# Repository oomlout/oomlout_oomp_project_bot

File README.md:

# oomlout_oomp_documentation_bot_v2

## actions

* action_setup.py -- sets up data and structure
* action_generate_kicad_from_eagle.py -- take all .brd eagle files, open in kicad and save as kicad_pcb and a kicad_sch file
* action_generate_kicad_outputs.py -- (not used anymore) generate the outputs using robo mouse, takes in a kicad_pcb and kicad_sch file
* action_generate_kibot_outputs.py -- all directories with kicad_pcb files get the kibot template from templates/kibot_template.yaml copied to them and kibot is run if the report.txt doesn't exist
* action_generate_image_resolutions.py -- generate resolutions of images
* action_generate_readmes -- generate all the readmes
* action_cleanup_project.py -- cleans up unwanted files from a project directory
* action_harvest_parts.py -- take the working_bom.csv and add parts_verbose to yaml file
* action_match_parts.py -- go trhough each part and match parts_verbose aprts with parts_oomp
* action_find_part.py -- go through all projects and compile a list of all the entries with  search term
* action_rescue_old_kicad_schematic.py -- go through and find all directories that have a kicad_pcb and a .sch file and no schematics generated. Open in kicad 5 and save.

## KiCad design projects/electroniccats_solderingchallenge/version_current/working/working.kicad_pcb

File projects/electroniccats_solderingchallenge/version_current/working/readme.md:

# OOMP Project  
## SolderingChallenge  by ElectronicCats  
  
oomp key: oomp_projects_flat_electroniccats_solderingchallenge  
(snippet of original readme)  
  
Introduction  
============  
  
This design is based on the work of [aspro648](https://github.com/aspro648) you can support him buying his stuff at [Tindie](https://www.tindie.com/products/MakersBox/smd-challenge/)  
  
This design was possible thanks to [Mouser electronics](https://iopscience.iop.org/journal/2041-8205/page/Focus_on_EHT), [Würth Elektronik](https://www.we-online.com/web/en/electronic_components/willkommen_pbs/Welcome.php) and [Makers GDL](https://makersgdl.com/) we really appreciate all your support to get this boards free for the Talent Land 2019.  

Test your surface mount soldering skills out, starting with a 1206 package and work your way down into the humanly possible solder device, the 0402. Powered by a CR2032 coin cell and Attiny 85 SOIC.   

Design Files  
============  
This project is designed using Open Source [KiCad](http://kicad.org/). Design files are located in the [Hw](Hw/) folder.  You can oogle the [schematic](Images/solderingChallenge.pdf).  
  
Firmware  
========  
This project is programed using the Open Source [Arduino](https://www.arduino.cc/). I use my Open Source [AVR Programming Shield](https://www.tindie.com/products/MakersBox/yet-another-programming-shield/) to program the Attiny. The firmware is located in the [firmware](Fw/) folder.  
  
Assembly Instructions  
=====================  
[Aspro648](https://github.com/aspro648) hav  
  full source readme at [readme_src.md](readme_src.md)  
  
source repo at: [https://github.com/ElectronicCats/SolderingChallenge](https://github.com/ElectronicCats/SolderingChallenge)  
## Board  

## Schematic  

[schematic pdf](working_schematic.pdf)  
## Images

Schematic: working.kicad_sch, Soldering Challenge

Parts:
BT1: Battery_Cell; 79523141
C1: 0.1uF; C_0805_2012Metric_Pad1.15x1.40mm_HandSolder
D1: 1206; LED_1206_3216Metric_Pad1.42x1.75mm_HandSolder
D2: 0805; LED_0805_2012Metric_Pad1.15x1.40mm_HandSolder
D3: 0603; LED_0603_1608Metric_Pad1.05x0.95mm_HandSolder
D4: 0402; LED_0402_1005Metric
J1: ISP; PinHeader_2x03_P2.54mm_Vertical
R1: 1206; R_1206_3216Metric_Pad1.42x1.75mm_HandSolder
R2: 0805; R_0805_2012Metric_Pad1.15x1.40mm_HandSolder
R3: 0603; R_0603_1608Metric_Pad1.05x0.95mm_HandSolder
R4: 0402; R_0402_1005Metric
TP1: PB0; TestPoint_Pad_1.0x1.0mm
TP2: PB1; TestPoint_Pad_1.0x1.0mm
TP3: PB2; TestPoint_Pad_1.0x1.0mm
TP4: PB3; TestPoint_Pad_1.0x1.0mm
TP5: PB4; TestPoint_Pad_1.0x1.0mm
TP6, TP7, TP8, TP9, TP10: GND; TestPoint_Pad_1.0x1.0mm
U1: ATtiny85-20SU; SOIJ-8_5.3x5.3mm_P1.27mm

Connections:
/MISO: D2.2 (A), J1.1, TP2.1, U1.6
/MOSI: D3.2 (A), J1.4, TP1.1, U1.5
/PB2: D1.2 (A), J1.3, TP3.1, U1.7
/PB3: D4.2 (A), TP4.1, U1.2
/PB4: U1.3
/RST: J1.5, U1.1
GND: BT1.2 (-), C1.2, J1.6, R1.1, R2.1, R3.1, R4.1, TP6.1, TP7.1, TP8.1, TP9.1, TP10.1, U1.4
unnamed: D1.1 (K), R1.2
unnamed: D2.1 (K), R2.2
unnamed: D3.1 (K), R3.2
unnamed: D4.1 (K), R4.2
VCC: BT1.1 (+), C1.1, J1.2, U1.8

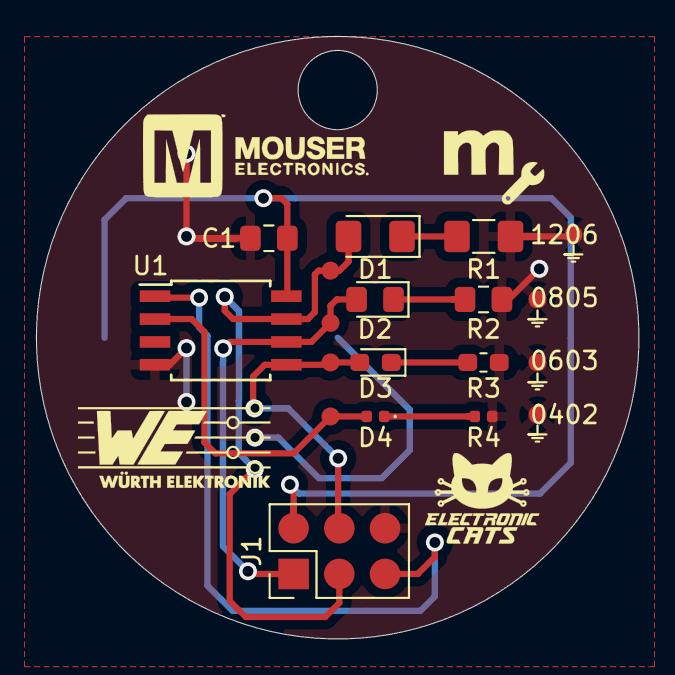
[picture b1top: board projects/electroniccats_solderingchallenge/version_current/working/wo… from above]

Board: 2 copper layers, 33.5 x 33.5 mm, 20 parts (1 on the bottom side), 11 nets.

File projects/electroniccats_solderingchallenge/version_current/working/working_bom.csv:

"Id";"Designator";"Footprint";"Quantity";"Designation";"Supplier and ref";
1;"R1";"R_1206_3216Metric_Pad1.42x1.75mm_HandSolder";1;"1206";;;
2;"R4";"R_0402_1005Metric";1;"0402";;;
3;"U1";"SOIJ-8_5.3x5.3mm_P1.27mm";1;"ATtiny85-20SU";;;
4;"D2";"LED_0805_2012Metric_Pad1.15x1.40mm_HandSolder";1;"0805";;;
5;"D3";"LED_0603_1608Metric_Pad1.05x0.95mm_HandSolder";1;"0603";;;
6;"D4";"LED_0402_1005Metric";1;"0402";;;
7;"R3";"R_0603_1608Metric_Pad1.05x0.95mm_HandSolder";1;"0603";;;
8;"R2";"R_0805_2012Metric_Pad1.15x1.40mm_HandSolder";1;"0805";;;
9;"C1";"C_0805_2012Metric_Pad1.15x1.40mm_HandSolder";1;"0.1uF";;;
10;"J1";"PinHeader_2x03_P2.54mm_Vertical";1;"ISP";;;
11;"G***,G***";"makersGDL";2;"LOGO";;;
12;"D1";"LED_1206_3216Metric_Pad1.42x1.75mm_HandSolder";1;"1206";;;
13;"G***,G***";"mouser";2;"LOGO";;;
14;"G***,G***";"electronic_cats_logo_4x3";2;"LOGO";;;
15;"G***,G***";"wurth";2;"LOGO";;;
16;"BT1";"79523141";1;"Battery_Cell";;;

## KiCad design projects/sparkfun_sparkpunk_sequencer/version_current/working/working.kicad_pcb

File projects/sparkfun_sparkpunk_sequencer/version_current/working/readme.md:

# Sparkpunk_Sequencer by sparkfun  
This is a harvested standardized copy of a project from github.  
The original project can be found at:  
https://github.com/sparkfun/Sparkpunk_Sequencer  
Please consult that link for additional, details, files, and license information.  
Note: It was auto harvested and if the original repo had more than one board file or anything out of the ordinary the files here are likely not representative.

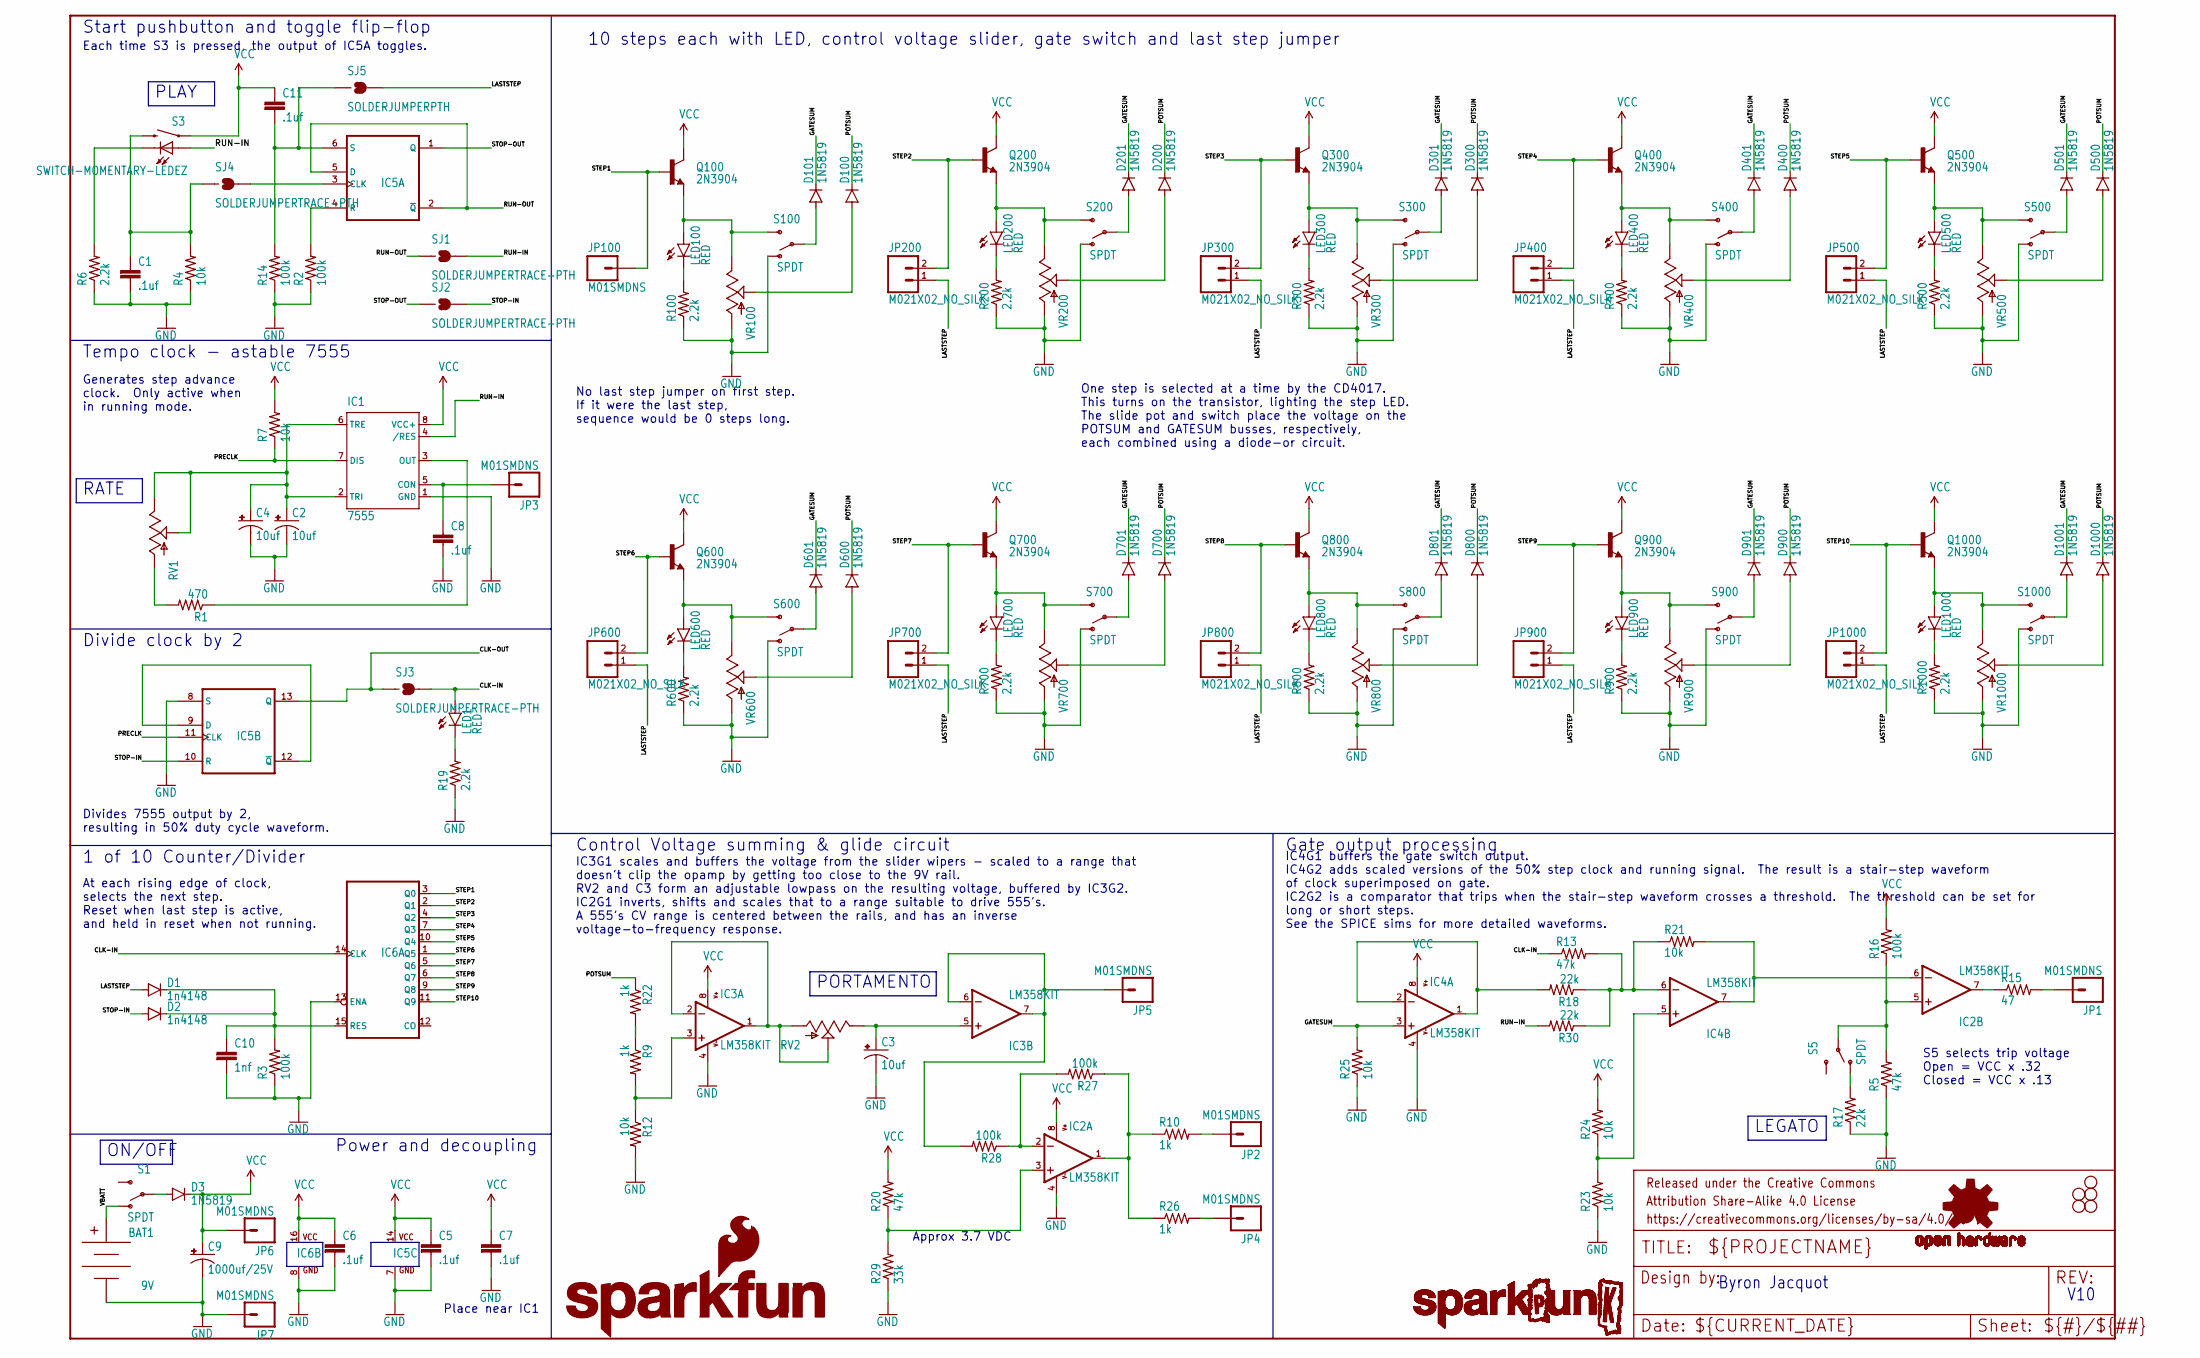
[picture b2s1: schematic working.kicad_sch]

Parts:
BAT1: 9V; BC9VPC_KIT
C1, C5, C6, C7, C8, C11: .1uf; CAP-PTH-SMALL-KIT
C2, C3, C4: 10uf; CPOL-RADIAL-10UF-25V-KIT
C9: 1000uf/25V; CPOL-RADIAL-1000UF-25V-KIT
C10: 1nf; CAP-PTH-SMALL-KIT
D1, D2: 1n4148; DIODE-1N4148-KIT
D3, D100, D101, D200, D201, D300, D301, D400, D401, D500, D501, D600, D601, D700, D701, D800, D801, D900, D901, D1000, D1001: 1N5819; DIODE-1N4001-KIT
FRAME1: FRAME-LEDGER; CREATIVE_COMMONS
IC1: 7555; DIP08-KIT
IC2, IC3, IC4: LM358KIT; DIP08-KIT
IC5: CD4013B; DIL14-KIT
IC6: CD4017KIT; DIL16-KIT
JP1, JP2, JP3, JP4, JP5, JP6, JP7, JP100: M01SMDNS; 1X01NS
JP200, JP300, JP400, JP500, JP600, JP700, JP800, JP900, JP1000: M021X02_NO_SILK; 1X02_NO_SILK
LED1, LED100, LED200, LED300, LED400, LED500, LED600, LED700, LED800, LED900, LED1000: RED; LED5MM-KIT
LOGO1: SPARKPUNK_LOGO.2_INCH_TALL; SPARKPUNK_LOGO_.2
LOGO2: OSHW-LOGOM; OSHW-LOGO-M
LOGO3: SPARKPUNK_LOGO.1INCH_TALL; SPARKPUNK_LOGO_.1
LOGO4: SFE_LOGO_NAME_FLAME.4_INCH; SFE_LOGO_NAME_FLAME_.4
Q100, Q200, Q300, Q400, Q500, Q600, Q700, Q800, Q900, Q1000: 2N3904; TO-92-AMMO
R1: 470; AXIAL-0.3EZ
R2, R3, R14, R16, R27, R28: 100k; AXIAL-0.3EZ
R4, R7, R12, R21, R23, R24, R25: 10k; AXIAL-0.3EZ
R5, R13, R20: 47k; AXIAL-0.3EZ
R6, R19, R100, R200, R300, R400, R500, R600, R700, R800, R900, R1000: 2.2k; AXIAL-0.3EZ
R9, R10, R22, R26: 1k; AXIAL-0.3EZ
R15: 47; AXIAL-0.3EZ
R17, R18, R30: 22k; AXIAL-0.3EZ
R29: 33k; AXIAL-0.3EZ
RV1, RV2: 10k; ALPS_POT_KIT
S1, S5, S100, S200, S300, S400, S500, S600, S700, S800, S900, S1000: SPDT; SWITCH-SPDT_KIT
S3: SWITCH-MOMENTARY-LEDEZ; TACTILE-PTH-LED-12MM-EZ
SJ1, SJ2, SJ3, SJ4: SOLDERJUMPERTRACE-PTH; SJ_2S-TRACE-PTH
SJ5: SOLDERJUMPERPTH; SJ_2S-PTH
STANDOFF1, STANDOFF2, STANDOFF3, STANDOFF5, STANDOFF6: STAND-OFF
VR100, VR200, VR300, VR400, VR500, VR600, VR700, VR800, VR900, VR1000: 10K; SLIDER-MEDIUM-KIT

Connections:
555OUT: IC1.3 (OUT), R1.P$1 (1)
BTN-OUT: C1.1, R4.P$2 (2), S3.2, SJ4.1
CLK-IN: IC6.14 (CLK), LED1.A, R13.P$1 (1), SJ3.2
CLK-OUT: IC5.13 (Q), SJ3.1
GATESUM: D101.C, D201.C, D301.C, D401.C, D501.C, D601.C, D701.C, D801.C, D901.C, D1001.C, IC4.3 (+IN), R25.P$2 (2)
GND: BAT1.V-, C1.2, C2.2 (-), C3.2 (-), C4.2 (-), C5.2, C6.2, C7.2, C8.2, C9.-, C10.2, IC1.1 (GND), IC2.4 (V-), IC3.4 (V-), IC4.4 (V-), IC5.7 (GND), IC5.8 (S), IC6.8 (GND), IC6.13 (ENA), JP7.1, R2.P$1 (1), R3.P$1 (1), R4.P$1 (1), R5.P$1 (1), R6.P$1 (1), R12.P$2 (2), R14.P$1 (1), R17.P$1 (1), R19.P$1 (1), R23.P$1 (1), R25.P$1 (1), R29.P$1 (1), R100.P$1 (1), R200.P$1 (1), R300.P$1 (1), R400.P$1 (1), R500.P$1 (1), R600.P$1 (1), R700.P$1 (1), R800.P$1 (1), R900.P$1 (1), R1000.P$1 (1), S100.1 (O), S200.1 (O), S300.1 (O), S400.1 (O), S500.1 (O), S600.1 (O), S700.1 (O), S800.1 (O), S900.1 (O), S1000.1 (O), VR100.BOTTOM (A), VR200.BOTTOM (A), VR300.BOTTOM (A), VR400.BOTTOM (A), VR500.BOTTOM (A), VR600.BOTTOM (A), VR700.BOTTOM (A), VR800.BOTTOM (A), VR900.BOTTOM (A), VR1000.BOTTOM (A)
LASTSTEP: D1.A, JP200.1, JP300.1, JP400.1, JP500.1, JP600.1, JP700.1, JP800.1, JP900.1, JP1000.1, SJ5.2
unnamed: LED100.A, Q100.1 (E), S100.3 (S), VR100.TOP (E)
unnamed: LED100.K (C), R100.P$2 (2)
unnamed: D101.A, S100.2
unnamed: D100.A, VR100.WIPER (S)
unnamed: R1.P$2 (2), RV1.P$3 (A)
unnamed: IC3.1 (OUT), IC3.2 (-IN), RV2.P$2 (S), RV2.P$3 (A)
unnamed: C8.1, IC1.5 (CON), JP3.1
unnamed: R6.P$2 (2), S3.C
unnamed: IC5.4 (R), R2.P$2 (2)
unnamed: C2.1 (+), C4.1 (+), IC1.2 (TRI), IC1.6 (TRE), RV1.P$1 (E), RV1.P$2 (S)
unnamed: IC4.1 (OUT), IC4.2 (-IN), R18.P$2 (2)
unnamed: LED1.K (C), R19.P$2 (2)
unnamed: C10.1, D1.C, D2.C, IC6.15 (RES), R3.P$2 (2)
unnamed: IC3.3 (+IN), R9.P$2 (2), R12.P$1 (1)
unnamed: R9.P$1 (1), R22.P$2 (2)
unnamed: IC2.2 (-IN), R27.P$2 (2), R28.P$1 (1)
unnamed: C3.1 (+), IC3.5 (+IN), RV2.P$1 (E)
unnamed: IC2.3 (+IN), R20.P$1 (1), R29.P$2 (2)
unnamed: JP1.1, R15.P$2 (2)
unnamed: IC5.3 (CLK), SJ4.2
unnamed: IC2.5 (+IN), R5.P$2 (2), R16.P$1 (1), S5.2
unnamed: IC2.7 (OUT), R15.P$1 (1)
unnamed: R17.P$2 (2), S5.1 (O)
unnamed: IC5.9 (D), IC5.12 (~Q)
unnamed: LED200.A, Q200.1 (E), S200.3 (S), VR200.TOP (E)
unnamed: LED200.K (C), R200.P$2 (2)
unnamed: D200.A, VR200.WIPER (S)
unnamed: D201.A, S200.2
unnamed: LED300.A, Q300.1 (E), S300.3 (S), VR300.TOP (E)
unnamed: LED300.K (C), R300.P$2 (2)
unnamed: D300.A, VR300.WIPER (S)
unnamed: D301.A, S300.2
unnamed: LED400.A, Q400.1 (E), S400.3 (S), VR400.TOP (E)
unnamed: LED400.K (C), R400.P$2 (2)
unnamed: D400.A, VR400.WIPER (S)
unnamed: D401.A, S400.2
unnamed: LED500.A, Q500.1 (E), S500.3 (S), VR500.TOP (E)
unnamed: LED500.K (C), R500.P$2 (2)
unnamed: D500.A, VR500.WIPER (S)
unnamed: D501.A, S500.2
unnamed: LED600.A, Q600.1 (E), S600.3 (S), VR600.TOP (E)
unnamed: LED600.K (C), R600.P$2 (2)
unnamed: D600.A, VR600.WIPER (S)
unnamed: D601.A, S600.2
unnamed: LED700.A, Q700.1 (E), S700.3 (S), VR700.TOP (E)
unnamed: LED700.K (C), R700.P$2 (2)
unnamed: D700.A, VR700.WIPER (S)
unnamed: D701.A, S700.2
unnamed: LED800.A, Q800.1 (E), S800.3 (S), VR800.TOP (E)
unnamed: LED800.K (C), R800.P$2 (2)
unnamed: D800.A, VR800.WIPER (S)
unnamed: D801.A, S800.2
unnamed: LED900.A, Q900.1 (E), S900.3 (S), VR900.TOP (E)
unnamed: LED900.K (C), R900.P$2 (2)
unnamed: D900.A, VR900.WIPER (S)
unnamed: D901.A, S900.2
unnamed: LED1000.A, Q1000.1 (E), S1000.3 (S), VR1000.TOP (E)
unnamed: LED1000.K (C), R1000.P$2 (2)
unnamed: D1000.A, VR1000.WIPER (S)
unnamed: D1001.A, S1000.2
unnamed: C11.2, IC5.6 (S), R14.P$2 (2), SJ5.1
unnamed: IC4.6 (-IN), R13.P$2 (2), R18.P$1 (1), R21.P$1 (1), R30.P$1 (1)
unnamed: IC3.6 (-IN), IC3.7 (OUT), JP5.1, R28.P$2 (2)
unnamed: IC2.1 (OUT), R10.P$1 (1), R26.P$1 (1), R27.P$1 (1)
unnamed: JP4.1, R26.P$2 (2)
unnamed: JP2.1, R10.P$2 (2)
unnamed: IC2.6 (-IN), IC4.7 (OUT), R21.P$2 (2)
unnamed: IC4.5 (+IN), R23.P$2 (2), R24.P$1 (1)
unnamed: D3.A, S1.2
POTSUM: D100.C, D200.C, D300.C, D400.C, D500.C, D600.C, D700.C, D800.C, D900.C, D1000.C, R22.P$1 (1)
PRECLK: IC1.7 (DIS), IC5.11 (CLK), R7.P$1 (1)
RUN-IN: IC1.4 (/RES), R30.P$2 (2), S3.A, SJ1.2
RUN-OUT: IC5.2 (~Q), IC5.5 (D), SJ1.1
STEP1: IC6.3 (Q0), JP100.1, Q100.2 (B)
STEP2: IC6.2 (Q1), JP200.2, Q200.2 (B)
STEP3: IC6.4 (Q2), JP300.2, Q300.2 (B)
STEP4: IC6.7 (Q3), JP400.2, Q400.2 (B)
STEP5: IC6.10 (Q4), JP500.2, Q500.2 (B)
STEP6: IC6.1 (Q5), JP600.2, Q600.2 (B)
STEP7: IC6.5 (Q6), JP700.2, Q700.2 (B)
STEP8: IC6.6 (Q7), JP800.2, Q800.2 (B)
STEP9: IC6.9 (Q8), JP900.2, Q900.2 (B)
STEP10: IC6.11 (Q9), JP1000.2, Q1000.2 (B)
STOP-IN: D2.A, IC5.10 (R), SJ2.2
STOP-OUT: IC5.1 (Q), SJ2.1
VBATT: BAT1.V+, S1.1 (O)
VCC: C5.1, C6.1, C7.1, C9.+, C11.1, D3.C, IC1.8 (VCC+), IC2.8 (V+), IC3.8 (V+), IC4.8 (V+), IC5.14 (VCC), IC6.16 (VCC), JP6.1, Q100.3 (C), Q200.3 (C), Q300.3 (C), Q400.3 (C), Q500.3 (C), Q600.3 (C), Q700.3 (C), Q800.3 (C), Q900.3 (C), Q1000.3 (C), R7.P$2 (2), R16.P$2 (2), R20.P$2 (2), R24.P$2 (2), S3.4 (1)

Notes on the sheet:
IC4G1 buffers the gate switch output. IC4G2 adds scaled versions of the 50% step clock and running signal. The result is a stair-step waveform of clock superimposed on gate. IC2G2 is a comparator that trips when the stair-step waveform crosses a threshold. The threshold can be set for long or short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
No last step jumper on first step. If it were the last step, sequence would be 0 steps long.
Divide clock by 2
Start pushbutton and toggle flip-flop
Byron Jacquot
Gate output processing
Control Voltage summing & glide circuit
One step is selected at a time by the CD4017. This turns on the transistor, lighting the step LED. The slide pot and switch place the voltage on the POTSUM and GATESUM busses, respectively, each combined using a diode-or circuit.
PORTAMENTO
LEGATO
V10
S5 selects trip voltage Open = VCC x .32 Closed = VCC x .13
10 steps each with LED, control voltage slider, gate switch and last step jumper
Divides 7555 output by 2, resulting in 50% duty cycle waveform.
PLAY
Each time S3 is pressed, the output of IC5A toggles.
Generates step advance clock. Only active when in running mode.
RATE
Approx 3.7 VDC
At each rising edge of clock, selects the next step. Reset when last step is active, and held in reset when not running.
ON/OFF
Power and decoupling
Place near IC1
Tempo clock - astable 7555
IC3G1 scales and buffers the voltage from the slider wipers - scaled to a range that doesn't clip the opamp by getting too close to the 9V rail. RV2 and C3 form an adjustable lowpass on the resulting voltage, buffered by IC3G2. IC2G1 inverts, shifts and scales that to a range suitable to drive 555'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
1 of 10 Counter/Divider

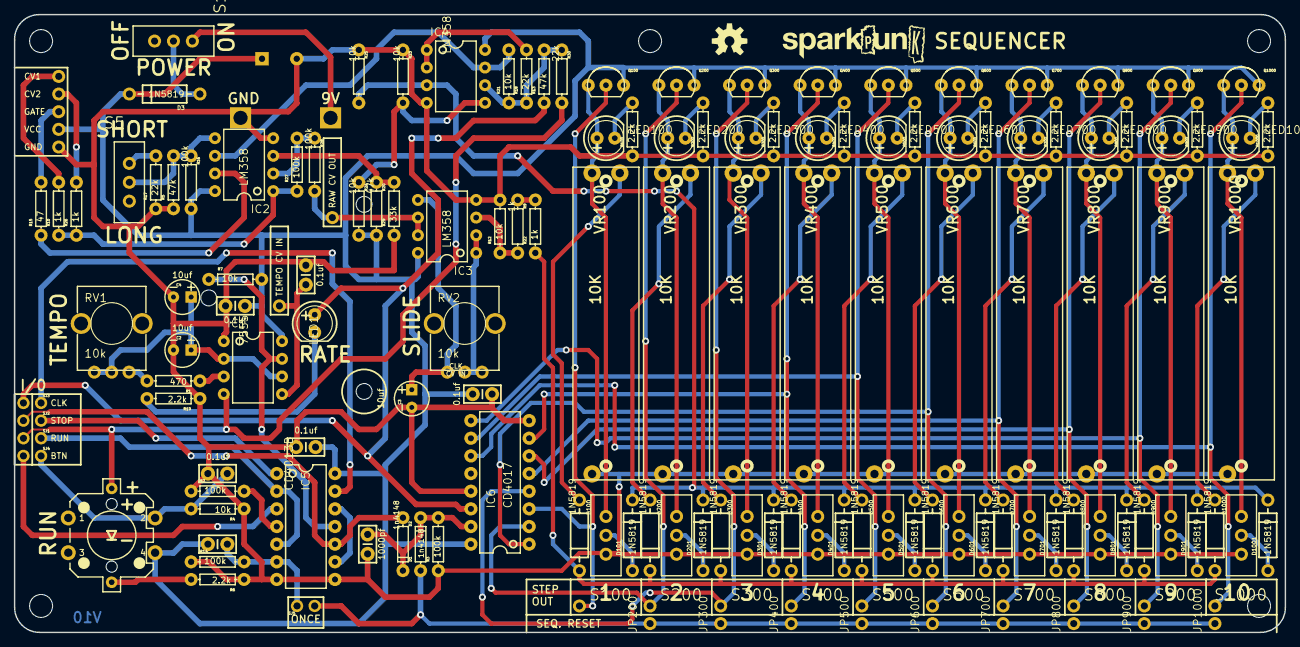
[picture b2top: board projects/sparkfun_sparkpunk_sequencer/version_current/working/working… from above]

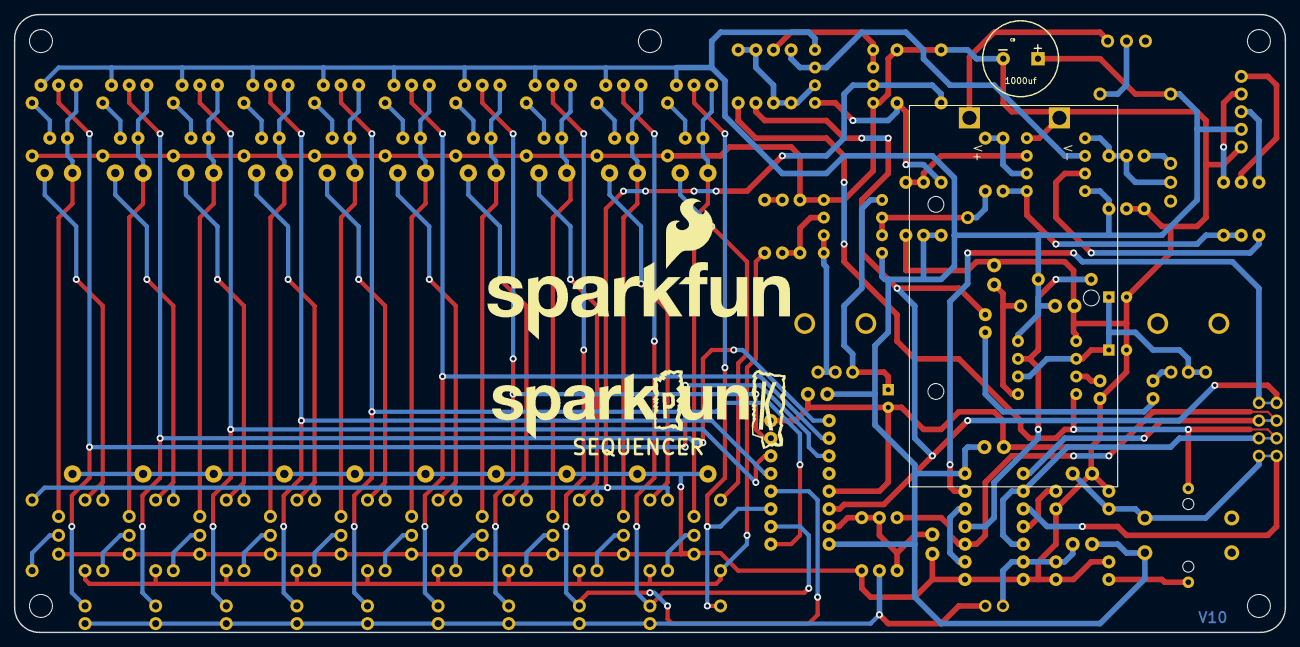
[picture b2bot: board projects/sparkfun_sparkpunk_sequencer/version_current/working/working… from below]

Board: 2 copper layers, 182.9 x 88.9 mm, 157 parts (4 on the bottom side), 94 nets.

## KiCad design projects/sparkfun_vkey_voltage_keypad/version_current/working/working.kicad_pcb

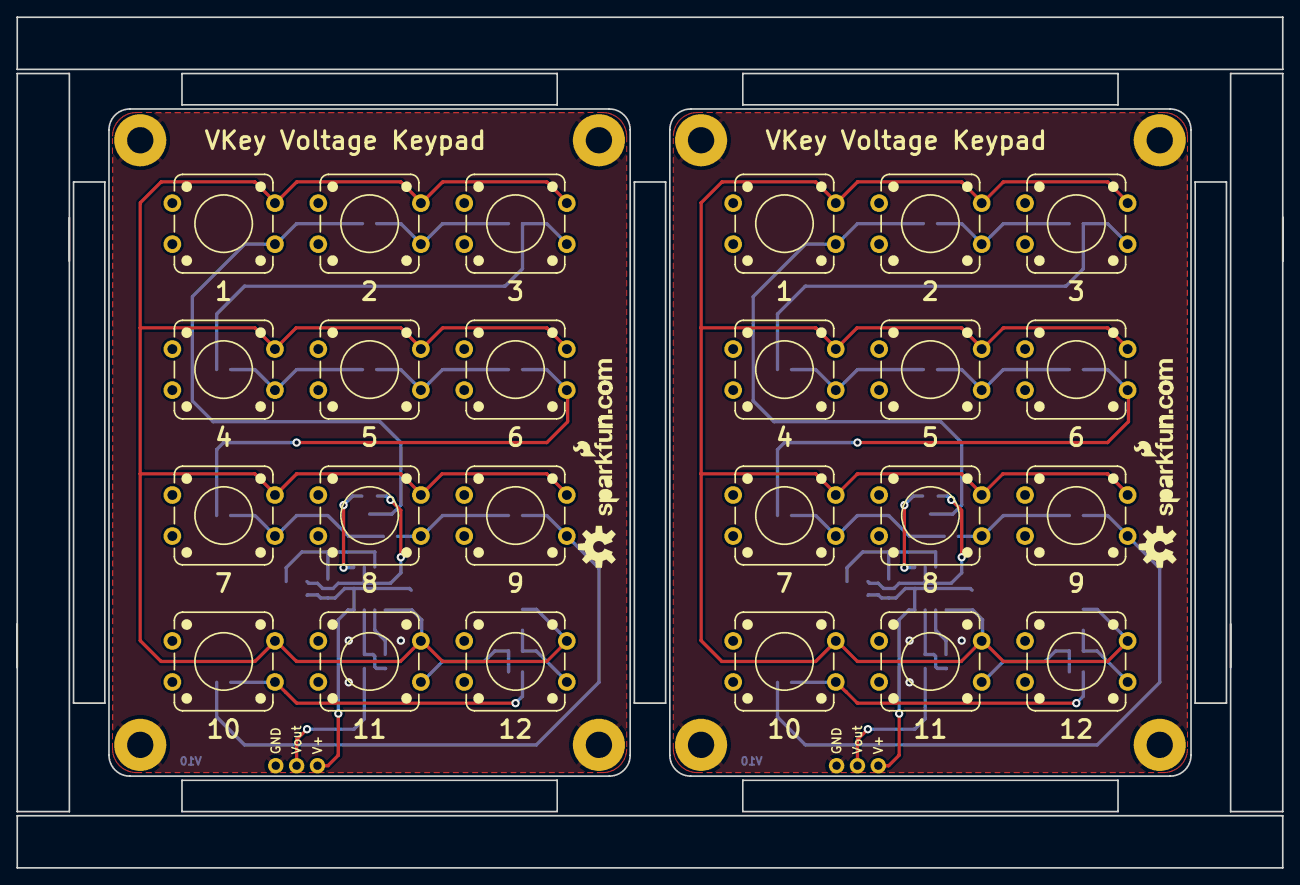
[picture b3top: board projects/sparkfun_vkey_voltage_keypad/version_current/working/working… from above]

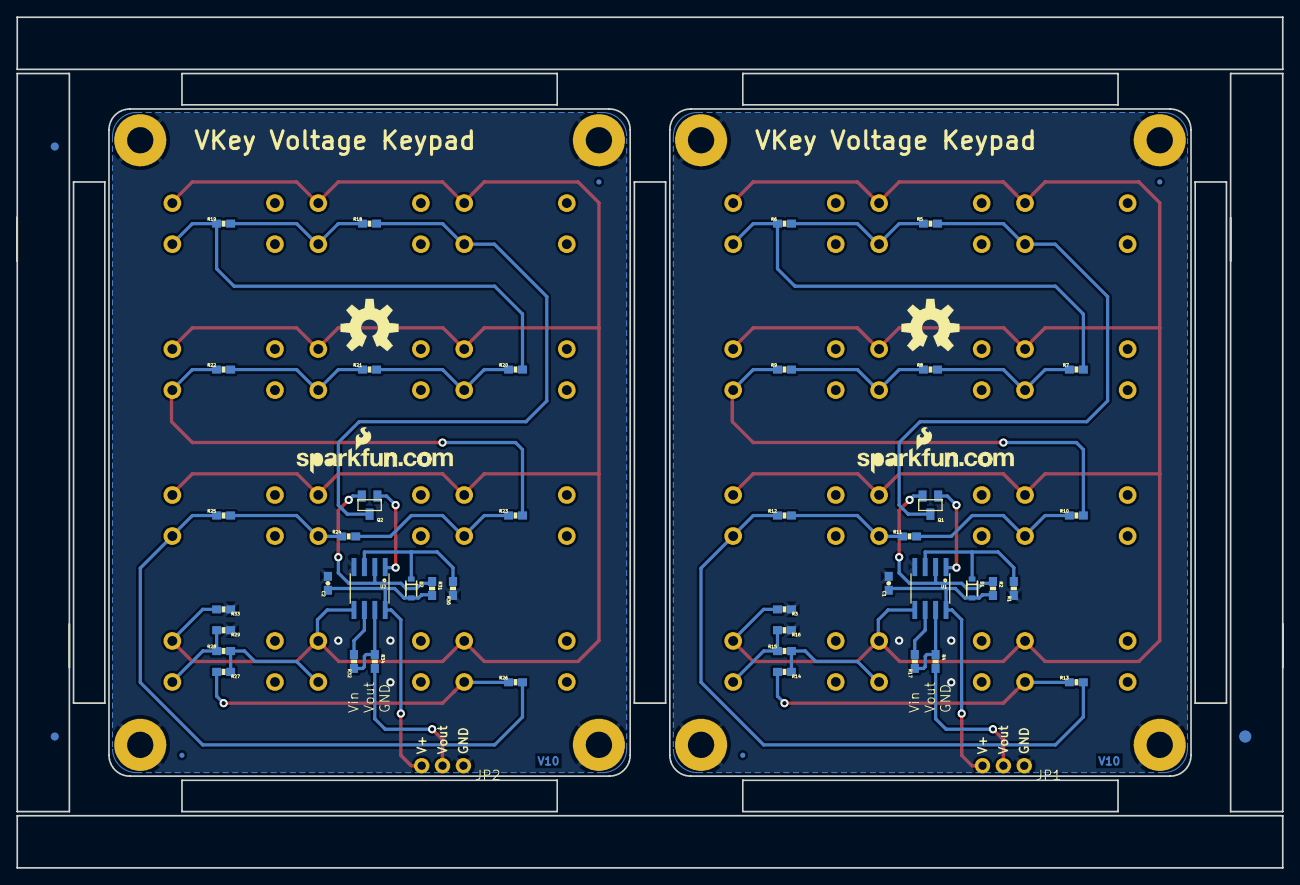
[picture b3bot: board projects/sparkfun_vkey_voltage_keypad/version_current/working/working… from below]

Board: 16 copper layers, 154.2 x 103.6 mm, 91 parts (55 on the bottom side), 42 nets.

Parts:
C1, C2: .01uF; 0603-CAP
D1, D2: BAS16; SOD-323
E$1: FIDUCIAL-1.5X3
E$2, E$3: FIDUCIAL-1X2.5
FID1, FID2, FID3, FID4: FIDUCIALUFIDUCIAL; MICRO-FIDUCIAL
JP1, JP2: POWER & OUTPUT; 1X03_NO_SILK
LOGO1, LOGO2, LOGO5, LOGO6: LOGO-SFENEW; SFE-NEW-WEBLOGO
LOGO3, LOGO7: OSHW-LOGOM; OSHW-LOGO-M
LOGO4, LOGO8: OSHW-LOGOL; OSHW-LOGO-L
Q1, Q2: MMBT3906; SOT23
R1, R30: 10k; 0603-RES
R2, R17, R31, R32: 1k; 0603-RES
R3, R33: 1meg; 0603-RES
R4, R34: 100; 0603-RES
R5, R6, R7, R8, R9, R10, R11, R12, R13, R14, R15, R16, R18, R19, R20, R21, R22, R23, R24, R25, R26, R27, R28, R29: 330; 0603-RES
S1, S2, S3, S4, S5, S6, S7, S8, S9, S10, S11, S12, S17, S18, S19, S20, S21, S22, S23, S24, S25, S26, S27, S28: SWITCH-MOMENTARY-212MM; TACTILE-PTH-12MM
S13, S14, S15, S16, S29, S30, S31, S32: STANDOFF_ELECTRICAL; STANDOFF-ELECTRICAL
U1, U2: LMV358; SO08

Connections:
5V: C1.1, D1.2, JP1.3, R2.2, U1.8
5V1: C2.1, D2.2, JP2.3, R31.2, U2.8
GND: C1.2, JP1.1, R1.1, R3.1, R16.1, S13.P1, S14.P1, S15.P1, S16.P1, U1.4
GND1: C2.2, JP2.1, R29.1, R30.1, R33.1, S29.P1, S30.P1, S31.P1, S32.P1, U2.4
unnamed: D1.1, R1.2, U1.3
unnamed: Q1.1, U1.1
unnamed: R3.2, S1.3, S2.3, S3.3, S4.3, S5.3, S6.3, S7.3, S8.3, S9.3, S10.3, S11.3, S12.3, U1.5
unnamed: R14.1, R15.2, S11.1
unnamed: Q1.2, R2.1, U1.2
unnamed: Q1.3, R5.2, S1.1
unnamed: R5.1, R6.2, S2.1
unnamed: R6.1, R7.2, S3.1
unnamed: R7.1, R8.2, S4.1
unnamed: R8.1, R9.2, S5.1
unnamed: R9.1, R10.2, S6.1
unnamed: R10.1, R11.2, S7.1
unnamed: R11.1, R12.2, S8.1
unnamed: R12.1, R13.2, S9.1
unnamed: R13.1, R14.2, S10.1
unnamed: R15.1, R16.2, S12.1
unnamed: R4.1, R17.1, U1.7
unnamed: R17.2, U1.6
unnamed: D2.1, R30.2, U2.3
unnamed: Q2.2, R31.1, U2.2
unnamed: Q2.3, R18.2, S17.1
unnamed: R18.1, R19.2, S18.1
unnamed: R19.1, R20.2, S19.1
unnamed: R20.1, R21.2, S20.1
unnamed: R21.1, R22.2, S21.1
unnamed: R22.1, R23.2, S22.1
unnamed: R24.1, R25.2, S24.1
unnamed: R25.1, R26.2, S25.1
unnamed: R26.1, R27.2, S26.1
unnamed: R28.1, R29.2, S28.1
unnamed: R27.1, R28.2, S27.1
unnamed: Q2.1, U2.1
unnamed: R33.2, S17.3, S18.3, S19.3, S20.3, S21.3, S22.3, S23.3, S24.3, S25.3, S26.3, S27.3, S28.3, U2.5
unnamed: R23.1, R24.2, S23.1
unnamed: R32.1, R34.1, U2.7
unnamed: R32.2, U2.6
VOUT: JP1.2, R4.2
VOUT1: JP2.2, R34.2

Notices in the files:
projects/solderparty_kmk_firmware/version_current/working/working.kicad_sch:
https://creativecommons.org/licenses/by-sa/4.0
Released under the Creative Commons
projects/sparkfun_redbot_buzzer/version_current/working/working.kicad_sch:
http://creativecommons.org/licenses/by-sa/3.0
parts and their libraries:
Released under the Creative Commons Attribution Share-Alike 4.0 License
